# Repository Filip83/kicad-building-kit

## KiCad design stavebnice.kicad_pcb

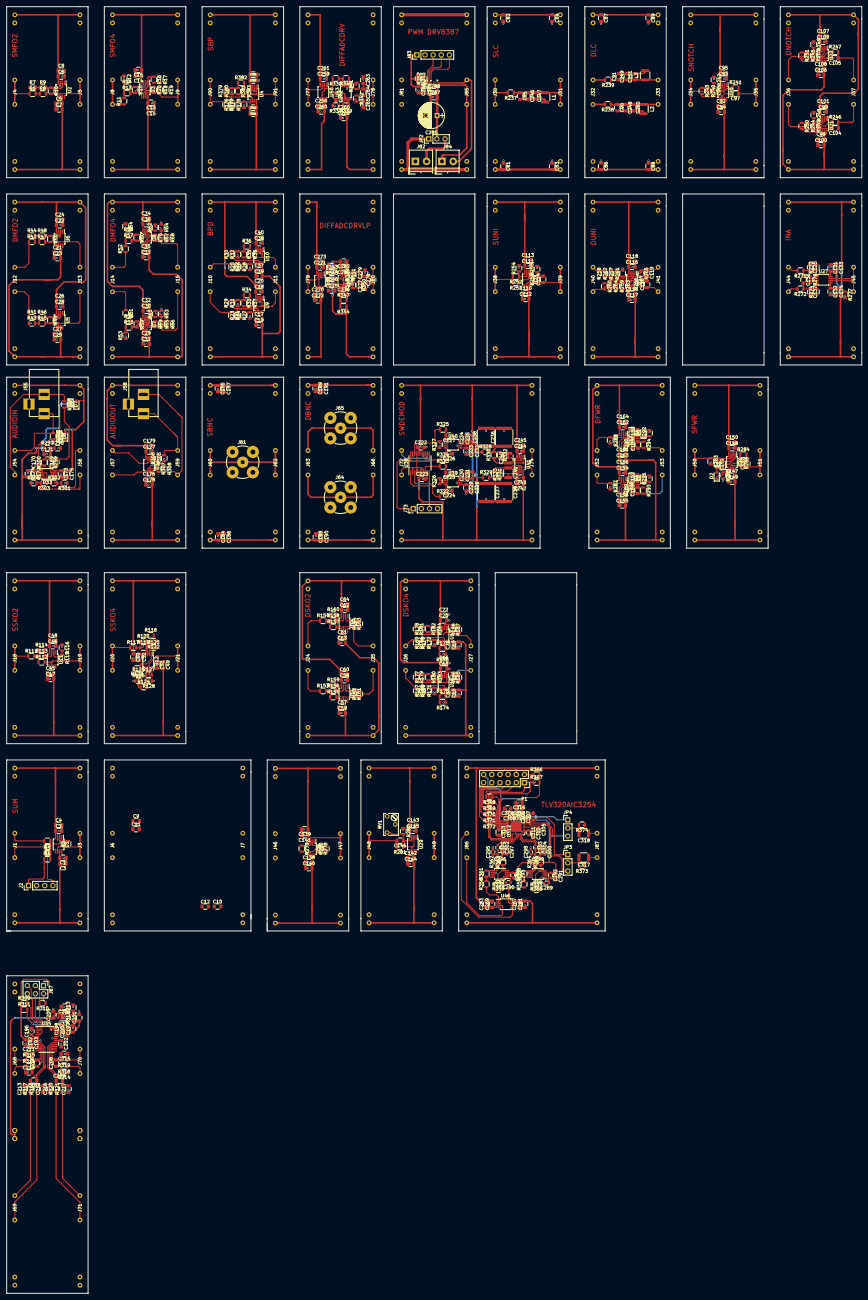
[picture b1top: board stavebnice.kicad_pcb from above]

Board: 2 copper layers, 266.7 x 401.3 mm, 676 parts (0 on the bottom side), 320 nets.

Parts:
C1, C2, C3, C4, C5, C6, C7, C8, C9, C10, C11, C12, C13, C14, C15, C16, C17, C18, C19, C20, C21, C22, C23, C24, C25, C26, C27, C28, C29, C30, C31, C32, C33, C34, C35, C36, C37, C38, C39, C40, C45, C46, C47, C48, C49, C50, C51, C52, C57, C58, C59, C60, C61, C62, C63, C64, C65, C66, C67, C68, C69, C70, C71, C72, C81, C82, C83, C84, C85, C86, C87, C88, C89, C90, C91, C92, C93, C94, C95, C96, C97, C98, C99, C100, C101, C102, C103, C104, C105, C106, C107, C108, C109, C110, C111, C112, C113, C114, C115, C116, C117, C118, C119, C120, C131, C132, C133, C134, C135, C136, C137, C138, C139, C140, C141, C142, C143, C144, C145, C146, C147, C148, C149, C150, C152, C153, C154, C155, C156, C159, C160, C161, C162, C163, C164, C169, C170, C172, C173, C174, C175, C176, C177, C178, C179, C184, C185, C186, C187, C188, C189, C190, C191, C206, C207, C208, C209, C210, C211, C212, C213, C214, C215, C216, C217, C246, C247, C248, C249, C250, C251, C258, C259, C260, C261, C263, C264, C265, C266, C267, C268, C269, C270, C271, C272, C273, C274, C275, C277, C278, C279, C280, C281, C282, C283, C319, C320, C321, C322: C; C_0805
C151, C157, C158: 47p; C_0805
C171, C205, C228, C231, C232, C235, C242, C245, C276, C287, C307, C308, C310, C316: 10u; C_0805
C192, C197, C315: 1u; C_0805
C193, C196, C198, C200, C202, C222, C223, C229, C230, C233, C234, C243, C244, C262, C284, C288: 100n; C_0805
C201, C286, C313: 4u7; C_0805
C203: 1n; C_0805
C224, C225, C226, C227: 1n5; C_0805
C236, C237, C238, C239: 470n; C_2220
C240, C241: 270n; C_1210
C285: 500u; CP_Radial_D8.0mm_P3.50mm
C289, C290, C292, C294, C295, C296, C297, C298, C299, C300, C301, C302, C303, C304, C305, C306, C309, C311, C312, C314: 100n; C_0603
C291, C293: 10u/5V; C_0805
C317, C318: C; C_1210
D1, D2, D3, D4, D5, D6: 1N4148; D_0805
D7, D8, D9, D10: D; D_0805
J1, J4, J6, J8, J10, J12, J14, J18, J20, J24, J26, J30, J32, J34, J36, J38, J40, J44, J46, J48, J50, J52, J54, J57, J60, J63, J68, J69, J70, J71, J72, J77, J79, J81, J86, J90: InConnector; my_io_connector
J2: Ext_Input; Pin_Header_Straight_1x04_Pitch2.54mm
J3, J5, J7, J9, J11, J13, J15, J19, J21, J25, J27, J31, J33, J35, J37, J39, J41, J45, J47, J49, J51, J53, J56, J59, J62, J66, J74, J78, J80, J85, J87, J91: OutConnector; my_io_connector
J55, J58: Audio-Jack-3; BARREL_JACK
J61, J64, J65: Conn_Coaxial; bnc-ci
J67: Conn_SPI; Pin_Header_Straight_2x03_Pitch2.54mm
J73: Conn_01x04; Pin_Header_Straight_1x04_Pitch2.54mm
J82, J84: Screw_Terminal_01x02; TerminalBlock_4UCON_19963_02x3.5mm_Straight
J83: Conn_01x05; Pin_Header_Straight_1x05_Pitch2.54mm
JP2, JP3, JP4: Jumper_NC_Dual; Pin_Header_Straight_1x03_Pitch2.54mm
L1, L2, L3: L; L_1210
P1: CONN_02X06; Socket_Strip_Straight_2x06
R1, R2, R3, R4, R5, R6, R7, R8, R9, R10, R11, R12, R13, R14, R15, R16, R17, R18, R19, R20, R21, R22, R23, R24, R25, R26, R27, R28, R29, R30, R31, R32, R33, R34, R35, R36, R37, R38, R41, R42, R43, R44, R45, R46, R47, R48, R49, R50, R51, R52, R53, R54, R55, R56, R57, R58, R59, R60, R61, R62, R63, R64, R65, R66, R67, R68, R69, R70, R111, R112, R113, R114, R115, R116, R117, R118, R119, R120, R121, R122, R123, R124, R125, R126, R127, R128, R153, R154, R155, R156, R157, R158, R159, R160, R161, R162, R163, R164, R165, R166, R167, R168, R169, R170, R171, R172, R173, R174, R175, R176, R177, R178, R179, R180, R181, R182, R183, R184, R185, R186, R187, R188, R237, R238, R239, R240, R241, R242, R243, R244, R245, R246, R247, R248, R249, R250, R251, R252, R253, R254, R255, R256, R257, R258, R259, R260, R261, R262, R263, R264, R265, R266, R271, R272, R273, R274, R276, R277, R278, R279, R280, R281, R282, R299, R300, R301, R302, R303, R304, R305, R306, R307, R308, R314, R315, R316, R317, R318, R319, R320, R321, R337, R338, R339, R340, R341, R342, R343, R345, R346, R350, R351, R352, R353, R373, R374, R375, R376, R377, R378, R379, R380, R381, R382, R383: R; R_0805
R283, R287, R288: 49.9; R_0805
R284, R285, R286, R289, R290, R291, R292, R293, R294: 1k; R_0805
R295, R296: 2k2; R_0805
R297, R298, R309, R310, R311, R366, R367: 10k; R_0805
R312, R313: 52k; R_0805
R322, R323, R324, R325: 5k; R_0805
R326, R327: 450; R_0805
R328, R329, R330, R331: 56k2; R_0805
R332, R333: 27k4; R_0805
R344, R347: 100k; R_0805
R348, R349: 2.49k; R_0805
R354, R355, R356, R357, R358, R359, R360, R361, R369, R370, R371, R372: 27; R_0805
R362, R363, R364, R365, R368: 10; R_0805
RV1: POT; Potentiometer_Trimmer_Bourns_3266W
U1, U2, U5, U6, U11, U14, U15, U20, U21, U22, U23, U28, U29, U50, U51: OPA333xxD; MSOP-8_3x3mm_Pitch0.65mm
U3, U7, U8, U12, U16, U17, U24, U30, U31, U32, U33, U34, U41, U44: ADA4807-2ARM; MSOP-8_3x3mm_Pitch0.65mm
U4, U9, U10, U46: ADA4075-2; MSOP-8_3x3mm_Pitch0.65mm
U27: AD8421; MSOP-8_3x3mm_Pitch0.65mm
U35: AD7124-4BRUZ; TSSOP-24_4.4x7.8mm_Pitch0.65mm
U37: ADM7170ACPZ; DFN-8-1EP_3x3mm_Pitch0.5mm
U38: ADG734BRU; TSSOP-20_4.4x6.5mm_Pitch0.65mm
U39, U40: AD8422BRMZ; MSOP-8_3x3mm_Pitch0.65mm
U43, U47, U48: LTC6363; MSOP-8_3x3mm_Pitch0.65mm
U45: DRV8837DSGR; WSON-8_2x2mm
U49: TLV320AIC3254; QFN-32-1EP_5x5mm_Pitch0.5mm

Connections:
+3.3VADC: C266.2, C268.2, C280.2, C282.2, J78.1, J80.1, R344.1, U43.3, U44.4
+3V3: C312.1, C313.1, C314.1, C315.1, C316.1, P1.4, P1.8, R366.2, R367.2, U49.6, U49.26, U49.30
+VSW: J82.2, JP2.3
/Codecs-IIS/Sheet5B5F145D//RESET: P1.12, U49.31
/Codecs-IIS/Sheet5B5F145D/Avdd: C291.1, C292.1, C293.1, C294.1, C306.1, C307.1, U47.3, U48.3, U49.24
/Codecs-IIS/Sheet5B5F145D/LRCK: P1.7, R370.2
/Codecs-IIS/Sheet5B5F145D/MCLK: P1.3, R368.2
/Codecs-IIS/Sheet5B5F145D/N1_N: C301.1, U49.13
/Codecs-IIS/Sheet5B5F145D/N1_P: C302.1, U49.14
/Codecs-IIS/Sheet5B5F145D/N2_N: C303.1, U49.15
/Codecs-IIS/Sheet5B5F145D/N2_P: C304.1, U49.16
/Codecs-IIS/Sheet5B5F145D/SCL: P1.2, R366.1, U49.9
/Codecs-IIS/Sheet5B5F145D/SCLK: P1.5, R369.2
/Codecs-IIS/Sheet5B5F145D/SDA: P1.1, R367.1, U49.10
/Codecs-IIS/Sheet5B5F145D/SIN: P1.9, R371.2
/Codecs-IIS/Sheet5B5F145D/SOUT: P1.11, R372.2
/PWM/DRV8837/8/IN1: J83.4, U45.6
/PWM/DRV8837/8/IN2: J83.5, U45.5
/PWM/DRV8837/8/~SLEEP: J83.3, R352.1, R353.2, U45.7
GND: C1.1, C2.2, C3.1, C4.2, C5.1, C6.2, C7.1, C8.2, C9.1, C10.2, C11.1, C12.2, C13.1, C14.2, C15.1, C16.2, C17.1, C18.2, C19.1, C20.2, C21.1, C22.2, C23.1, C24.2, C25.1, C26.2, C27.1, C28.2, C29.1, C30.2, C31.1, C32.2, C33.1, C34.2, C35.1, C36.2, C37.1, C38.2, C39.1, C40.2, C45.1, C46.2, C47.1, C48.2, C49.1, C50.2, C51.1, C52.2, C57.1, C58.2, C59.1, C60.2, C61.1, C62.2, C63.1, C64.2, C65.1, C66.2, C67.1, C68.2, C69.1, C70.2, C71.1, C72.2, C81.1, C82.2, C83.1, C84.2, C85.2, C86.1, C87.2, C88.1, C89.2, C90.2, C91.2, C92.1, C93.2, C94.1, C95.2, C98.1, C99.2, C100.1, C101.2, C106.1, C107.2, C108.1, C109.2, C110.1, C111.2, C112.1, C113.2, C115.1, C116.2, C117.1, C118.2, C131.1, C132.2, C133.1, C134.2, C135.1, C137.2, C138.1, C139.2, C140.1, C141.2, C142.1, C143.2, C144.1, C145.2, C147.1, C148.2, C149.1, C150.2, C153.1, C154.2, C155.1, C156.2, C161.1, C162.2, C163.1, C164.2, C171.1, C172.1, C173.2, C174.1, C175.2, C176.1, C177.2, C178.1, C179.2, C184.1, C185.2, C186.1, C187.2, C188.1, C189.2, C190.1, C191.2, C192.2, C193.2, C222.2, C223.2, C224.1, C225.1, C226.1, C227.1, C228.2, C229.2, C230.2, C231.2, C232.2, C233.2, C234.2, C235.2, C236.2, C237.2, C238.2, C239.2, C242.2, C243.2, C244.2, C245.2, C246.2, C247.2, C248.2, C249.2, C250.2, C251.2, C258.1, C259.2, C260.1, C261.2, C262.2, C263.1, C265.2, C266.1, C267.1, C268.1, C269.2, C270.1, C271.2, C272.1, C273.2, C274.2, C276.2, C277.1, C279.2, C280.1, C281.1, C282.1, C283.2, C284.2, C285.2, C286.2, C287.1, C288.1, C289.2, C290.2, C291.2, C292.2, C293.2, C294.2, C295.2, C297.1, C298.2, C300.1, C305.2, C306.2, C307.2, C308.2, C309.2, C310.2, C311.2, C312.2, C313.2, C314.2, C315.2, C316.2, C319.1, C320.2, C321.1, C322.2, J1.2, J1.5, J2.2, J2.3, J3.2, J3.5, J4.2, J4.5, J5.2, J5.5, J6.2, J6.5, J7.2, J7.5, J8.2, J8.5, J9.2, J9.5, J10.2, J10.5, J11.2, J11.5, J12.2, J12.5, J13.2, J13.5, J14.2, J14.5, J15.2, J15.5, J18.2, J18.5, J19.2, J19.5, J20.2, J20.5, J21.2, J21.5, J24.2, J24.5, J25.2, J25.5, J26.2, J26.5, J27.2, J27.5, J30.2, J30.5, J31.2, J31.5, J32.2, J32.5, J33.2, J33.5, J34.2, J34.5, J35.2, J35.5, J36.2, J36.5, J37.2, J37.5, J38.2, J38.5, J39.2, J39.5, J40.2, J40.5, J41.2, J41.5, J44.2, J44.5, J45.2, J45.5, J46.2, J46.5, J47.2, J47.5, J48.2, J48.5, J49.2, J49.5, J50.2, J50.5, J51.2, J51.5, J52.2, J52.5, J53.2, J53.5, J54.2, J54.5, J55.3, J56.2, J56.5, J57.2, J57.5, J58.3, J59.2, J59.5, J60.2, J60.5, J61.2, J62.2, J62.5, J63.2, J63.5, J64.2, J65.2, J66.2, J66.5, J67.1, J68.5, J69.1, J69.2, J70.2, J70.5, J71.2, J71.5, J72.2, J72.5, J73.2, J73.4, J74.2, J74.5, J77.2, J77.5, J78.2, J78.5, J78.6, J79.2, J79.5, J80.2, J80.5, J80.6, J81.2, J81.5, J82.1, J83.2, J85.2, J85.5, J86.2, J86.5, J87.2, J87.5, J90.2, J90.5, J91.2, J91.5, L1.2, L2.2, L3.2, P1.6, P1.10, R7.1, R12.1, R17.1, R27.1, R28.1, R31.1, R32.1, R43.1, R44.1, R53.1, R54.1, R63.1, R64.1, R114.1, R116.1, R120.1, R122.1, R126.1, R128.1, R159.1, R160.1, R162.1, R164.1, R171.1, R172.1, R174.1, R176.1, R183.1, R184.1, R186.1, R188.1, R242.1, R248.1, R249.1, R254.2, R255.2, R261.2, R262.2, R263.2, R264.2, R273.2, R274.1, R277.2, R278.2, R282.1, R283.2, R285.2, R287.2, R288.2, R291.2, R292.2, R298.2, R301.1, R304.1, R305.1, R308.1, R337.2, R347.2, R353.1, R355.1, R357.1, R373.1, R374.1, R378.1, R380.1, RV1.1, RV1.2, U1.3, U2.3, U3.3, U3.5, U4.2, U5.3, U6.3, U7.3, U7.5, U8.3, U8.5, U9.2, U10.2, U38.4, U38.6, U38.9, U38.14, U38.19, U39.6, U40.6, U41.3, U41.5, U43.6, U44.8, U45.4, U45.9, U47.6, U48.6, U49.7, U49.12, U49.17, U49.28, U49.33
GNDA: C196.2, C197.2, C198.2, C200.2, C201.2, C202.2, C203.2, C205.2, C210.1, C211.1, C212.1, C213.1, C214.1, C215.1, C216.1, C217.1, R313.2, U35.7, U35.19, U37.6, U37.9
unnamed: C96.1, R242.2, U20.3
unnamed: C96.2, J34.3, J34.4, R240.2, R241.1
unnamed: C97.1, J35.3, J35.4, R241.2
unnamed: C97.2, R243.2, U20.6
unnamed: C102.1, R248.2, U21.3
unnamed: C102.2, J36.3, R244.2, R246.1
unnamed: C103.1, R249.2, U22.3
unnamed: C103.2, J36.4, R245.2, R247.1
unnamed: C104.1, J37.3, R246.2
unnamed: C104.2, R250.2, U21.6
unnamed: C105.1, J37.4, R247.2
unnamed: C105.2, R251.2, U22.6
unnamed: C114.1, J39.3, J39.4, R256.1, U23.6
unnamed: C114.2, R253.1, R255.1, R256.2, U23.2
unnamed: C119.1, J41.4, R265.1, U24.1
unnamed: C119.2, R258.1, R262.1, R265.2, U24.2
unnamed: C120.1, J41.3, R266.1, U24.7
unnamed: C120.2, R260.1, R264.1, R266.2, U24.6
unnamed: C135.2, C136.1, R271.1, R273.1, U27.1
unnamed: C136.2, C137.1, R272.1, R274.2, U27.4
unnamed: C146.1, R282.2, RV1.3, U29.3
unnamed: C146.2, J48.3, J48.4, R281.2
unnamed: C151.1, D1.2, R284.1, U30.2
unnamed: C151.2, D1.1, D2.2, U30.1
unnamed: C152.1, J51.3, J51.4, R286.2, U30.7
unnamed: C152.2, R284.2, R286.1, U30.6
unnamed: C157.1, D3.2, R289.1, U31.2
unnamed: C157.2, D3.1, D5.2, U31.1
unnamed: C158.1, D4.2, R290.1, U32.2
unnamed: C158.2, D4.1, D6.2, U32.1
unnamed: C159.1, J53.3, R293.2, U31.7
unnamed: C159.2, R289.2, R293.1, U31.6
unnamed: C160.1, J53.4, R294.2, U32.7
unnamed: C160.2, R290.2, R294.1, U32.6
unnamed: C169.1, R299.2, U33.3
unnamed: C169.2, D7.2, D9.1, R295.2
unnamed: C170.1, R300.1, U33.5
unnamed: C170.2, D8.2, D10.1, R296.2
unnamed: C171.2, R297.2, R298.1, R299.1, R300.2
unnamed: C196.1, U35.5
unnamed: C197.1, C198.1, C201.1, R312.1, U35.22, U37.1, U37.2
unnamed: C200.1, U35.20
unnamed: C202.1, U35.18
unnamed: C203.1, U37.4
unnamed: C206.1, C210.2, R314.2, U35.10
unnamed: C206.2, C211.2, R315.2, U35.11
unnamed: C207.1, C212.2, R316.2, U35.8
unnamed: C207.2, C213.2, R317.2, U35.9
unnamed: C208.1, C214.2, R318.2, U35.15
unnamed: C208.2, C215.2, R319.2, U35.14
unnamed: C209.1, C216.2, R320.2, U35.17
unnamed: C209.2, C217.2, R321.2, U35.16
unnamed: C224.2, R322.2, U39.4
unnamed: C225.2, R323.2, U39.1
unnamed: C226.2, R324.2, U40.4
unnamed: C227.2, R325.2, U40.1
unnamed: C236.1, C238.1, R328.2, R330.2, R332.1
unnamed: C237.1, C239.1, R329.2, R331.2, R333.1
unnamed: C240.1, J74.4, R330.1, U41.1
unnamed: C240.2, R332.2, U41.2
unnamed: C241.1, J74.3, R331.1, U41.7
unnamed: C241.2, R333.2, U41.6
unnamed: C85.1, C246.1, C247.1, J31.3, J31.4, L1.1, R237.1
unnamed: C90.1, C248.1, C250.1, J33.3, L2.1, R238.1
unnamed: C91.1, C249.1, C251.1, J33.4, L3.1, R239.1
unnamed: C262.1, U43.2
unnamed: C263.2, C264.1, J78.4, R341.1
unnamed: C264.2, C265.1, J78.3, R342.1
unnamed: C274.1, R343.2, R345.1, R346.1
unnamed: C275.1, R345.2, R348.1, R350.2, U44.7
unnamed: C275.2, R346.2, U44.6
unnamed: C276.1, R344.2, R347.1, U44.3, U44.5
unnamed: C277.2, C278.1, J80.3, R350.1
unnamed: C278.2, C279.1, J80.4, R351.1
unnamed: C285.1, C287.2, C288.2, JP2.2, U45.1
unnamed: C289.1, U48.2
unnamed: C290.1, U47.2
unnamed: C295.1, C296.2, C301.2, R362.2
unnamed: C296.1, C297.2, C302.2, R363.2
unnamed: C298.1, C299.2, C303.2, R364.2
unnamed: C299.1, C300.2, C304.2, R365.2
unnamed: C305.1, U49.20, U49.21
unnamed: C308.1, C309.1, U49.29
unnamed: C310.1, C311.1, U49.18
unnamed: C317.1, J87.3
unnamed: C317.2, JP3.2, R373.2
unnamed: C318.1, J87.4
unnamed: C318.2, JP4.2, R374.2
unnamed: D2.1, R285.1, U30.5
unnamed: D5.1, R291.1, U31.5
unnamed: D6.1, R292.1, U32.5
unnamed: J1.3, R1.2
unnamed: J1.4, R2.2
unnamed: J2.1, R4.1
unnamed: J2.4, R3.1
unnamed: J3.3, J3.4, R5.1, U1.6
unnamed: J4.3, J4.4, R6.1
unnamed: J5.3, J5.4, R8.2, R10.2, U2.6
unnamed: J7.3, J7.4
unnamed: J8.3, J8.4, R11.1
unnamed: J9.3, J9.4, R18.2, R20.2, U3.7
unnamed: J10.3, R21.1
unnamed: J10.4, R22.1
unnamed: J11.3, R33.2, R37.2, U9.1
unnamed: J11.4, R35.2, R38.2, U10.1
unnamed: J12.3, R41.1
unnamed: J12.4, R42.1
unnamed: J13.3, R45.2, R49.2, U5.6
unnamed: J13.4, R47.2, R50.2, U6.6
unnamed: J14.3, R51.1
unnamed: J14.4, R52.1
unnamed: J15.3, R65.2, R69.2, U7.7
unnamed: J15.4, R67.2, R70.2, U8.7
unnamed: J18.3, J18.4, R111.1
unnamed: J19.3, J19.4, R112.2, R115.2, U11.6
unnamed: J20.3, J20.4, R117.1
unnamed: J21.3, J21.4, R124.2, R127.2, U12.7
unnamed: J24.3, R153.1
unnamed: J24.4, R154.1
unnamed: J25.3, R155.2, R161.2, U14.6
unnamed: J25.4, R157.2, R163.2, U15.6
unnamed: J26.3, R165.1
unnamed: J26.4, R166.1
unnamed: J27.3, R179.2, R185.2, U16.1
unnamed: J27.4, R181.2, R187.2, U17.1
unnamed: J30.3, J30.4, R237.2
unnamed: J32.3, R238.2
unnamed: J32.4, R239.2
unnamed: J38.3, J38.4, R252.2, R253.2
unnamed: J40.3, R259.2, R260.2
unnamed: J40.4, R257.2, R258.2
unnamed: J44.3, R272.2
unnamed: J44.4, R271.2
unnamed: J45.3, R277.1, U27.6
unnamed: J45.4, U27.7
unnamed: J47.3, J47.4, R279.1, U28.3
unnamed: J49.3, J49.4
unnamed: J50.3, J50.4, R283.1, U30.3
unnamed: J52.3, R287.1, U31.3
unnamed: J52.4, R288.1, U32.3
unnamed: J54.3, J55.2, R295.1
unnamed: J54.4, J55.1, R296.1
unnamed: J56.3, R303.2, R304.2, U33.7
unnamed: J56.4, R301.2, R302.2, U33.1
unnamed: J57.3, U34.5
unnamed: J57.4, U34.3
unnamed: J58.1, J59.4, R305.2, R306.2, U34.1
unnamed: J58.2, J59.3, R307.2, R308.2, U34.7
unnamed: J60.3, J60.4, J61.1, J62.3, J62.4
unnamed: J63.3, J64.1, J66.3
unnamed: J63.4, J65.1, J66.4
unnamed: J67.3, R310.2, U35.4
unnamed: J67.4, U35.2
unnamed: J67.5, U35.1
unnamed: J67.6, R309.2, U35.24
unnamed: J68.3, R314.1
unnamed: J68.4, R315.1
unnamed: J69.3, R316.1
unnamed: J69.4, R317.1
unnamed: J70.3, R318.1
unnamed: J70.4, R319.1
unnamed: J71.3, R320.1
unnamed: J71.4, R321.1
unnamed: J72.3, J72.4, U38.2, U38.7, U38.12, U38.17
unnamed: J73.1, U38.11, U38.20
unnamed: J73.3, U38.1, U38.10
unnamed: J77.3, J77.4, U50.3
unnamed: J79.3, J79.4, U51.3
unnamed: J84.1, J85.3, U45.2
unnamed: J84.2, J85.4, U45.3
unnamed: J86.3, U46.3
unnamed: J86.4, U46.5
unnamed: J90.3, J90.4, R375.1
unnamed: J91.3, J91.4, R381.2, R383.2, U4.1
unnamed: JP3.1, U49.25
unnamed: JP3.3, U49.22
unnamed: JP4.1, U49.27
unnamed: JP4.3, U49.23
unnamed: R1.1, R2.1, R3.2, R4.2, R5.2, U1.2
unnamed: R6.2, R7.2, R8.1, R9.1
unnamed: R9.2, R10.1, U2.2
unnamed: R11.2, R12.2, R13.1, R14.1
unnamed: R13.2, R15.2, R16.1, U3.1
unnamed: R14.2, R15.1, U3.2
unnamed: R16.2, R17.2, R18.1, R19.1
unnamed: R19.2, R20.1, U3.6
unnamed: R21.2, R23.1, R24.1
unnamed: R22.2, R25.1, R26.1
unnamed: R23.2, R29.1, U9.6, U9.7
unnamed: R24.2, R27.2, U9.5
unnamed: R25.2, R30.1, U10.6, U10.7
unnamed: R26.2, R28.2, U10.5
unnamed: R29.2, R31.2, R33.1, R34.1
unnamed: R30.2, R32.2, R35.1, R36.1
unnamed: R34.2, R37.1, U9.3
unnamed: R36.2, R38.1, U10.3
unnamed: R41.2, R43.2, R45.1, R46.1
unnamed: R42.2, R44.2, R47.1, R48.1
unnamed: R46.2, R49.1, U5.2
unnamed: R48.2, R50.1, U6.2
unnamed: R51.2, R53.2, R55.1, R56.1
unnamed: R52.2, R54.2, R57.1, R58.1
unnamed: R55.2, R59.2, R61.1, U7.1
unnamed: R56.2, R59.1, U7.2
unnamed: R57.2, R60.2, R62.1, U8.1
unnamed: R58.2, R60.1, U8.2
unnamed: R61.2, R63.2, R65.1, R66.1
unnamed: R62.2, R64.2, R67.1, R68.1
unnamed: R66.2, R69.1, U7.6
unnamed: R68.2, R70.1, U8.6
unnamed: R111.2, R112.1, R113.1
unnamed: R113.2, R114.2, U11.3
unnamed: R115.1, R116.2, U11.2
unnamed: R117.2, R118.1, R119.1
unnamed: R118.2, R121.2, R123.1, U12.1
unnamed: R119.2, R120.2, U12.3
unnamed: R121.1, R122.2, U12.2
unnamed: R123.2, R124.1, R125.1
unnamed: R125.2, R126.2, U12.5
unnamed: R127.1, R128.2, U12.6
unnamed: R153.2, R155.1, R156.1
unnamed: R154.2, R157.1, R158.1
unnamed: R156.2, R159.2, U14.3
unnamed: R158.2, R160.2, U15.3
unnamed: R161.1, R162.2, U14.2
unnamed: R163.1, R164.2, U15.2
unnamed: R165.2, R167.1, R168.1
unnamed: R166.2, R169.1, R170.1
unnamed: R167.2, R173.2, R177.1, U16.7
unnamed: R168.2, R171.2, U16.5
unnamed: R169.2, R175.2, R178.1, U17.7
unnamed: R170.2, R172.2, U17.5
unnamed: R173.1, R174.2, U16.6
unnamed: R175.1, R176.2, U17.6
unnamed: R177.2, R179.1, R180.1
unnamed: R178.2, R181.1, R182.1
unnamed: R180.2, R183.2, U16.3
unnamed: R182.2, R184.2, U17.3
unnamed: R185.1, R186.2, U16.2
unnamed: R187.1, R188.2, U17.2
unnamed: R240.1, R243.1, U20.2
unnamed: R244.1, R250.1, U21.2
unnamed: R245.1, R251.1, U22.2
unnamed: R252.1, R254.1, U23.3
unnamed: R257.1, R261.1, U24.3
unnamed: R259.1, R263.1, U24.5
unnamed: R276.1, U27.2
unnamed: R276.2, U27.3
unnamed: R278.1, R280.2, U28.2
unnamed: R279.2, R280.1, U28.6
unnamed: R281.1, U29.2, U29.6
unnamed: R302.1, U33.2
unnamed: R303.1, U33.6
unnamed: R306.1, U34.2
unnamed: R307.1, U34.6
unnamed: R311.2, U35.23
unnamed: R312.2, R313.1, U37.3
unnamed: R322.1, U38.3
unnamed: R323.1, U38.8
unnamed: R324.1, U38.13
unnamed: R325.1, U38.18
unnamed: R326.1, U39.3
unnamed: R326.2, U39.2
unnamed: R327.1, U40.3
unnamed: R327.2, U40.2
unnamed: R328.1, U40.7
unnamed: R329.1, U39.7
unnamed: R337.1, R339.2, U43.1
unnamed: R338.1, R340.2, U43.8
unnamed: R338.2, U50.2, U50.6
unnamed: R339.1, R342.2, U43.4
unnamed: R340.1, R341.2, U43.5
unnamed: R343.1, U51.2, U51.6
unnamed: R348.2, R349.1, U44.2
unnamed: R349.2, R351.2, U44.1
unnamed: R354.1, U46.6, U46.7
unnamed: R354.2, R358.1, U48.8
unnamed: R355.2, R359.1, U47.1
unnamed: R356.1, U46.1, U46.2
unnamed: R356.2, R361.1, U47.8
unnamed: R357.2, R360.1, U48.1
unnamed: R358.2, R364.1, U48.5
unnamed: R359.2, R363.1, U47.4
unnamed: R360.2, R365.1, U48.4
unnamed: R361.2, R362.1, U47.5
unnamed: R368.1, U49.1
unnamed: R369.1, U49.2
unnamed: R370.1, U49.3
unnamed: R371.1, U49.4
unnamed: R372.1, U49.5
unnamed: R375.2, R376.1, R377.1
unnamed: R376.2, R379.1, U4.6, U4.7
unnamed: R377.2, R378.2, U4.5
unnamed: R379.2, R380.2, R381.1, R382.1
unnamed: R382.2, R383.1, U4.3
V+: C284.1, C286.1, J83.1, R352.2, U45.8
VBUS: C192.1, C193.1, J67.2, R309.1, R310.1, R311.1, U35.6
VCC: C1.2, C3.2, C5.2, C7.2, C9.2, C11.2, C13.2, C15.2, C17.2, C19.2, C21.2, C23.2, C25.2, C27.2, C29.2, C31.2, C33.2, C35.2, C37.2, C39.2, C45.2, C47.2, C49.2, C51.2, C57.2, C59.2, C61.2, C63.2, C65.2, C67.2, C69.2, C71.2, C81.2, C83.2, C86.2, C88.2, C92.2, C94.2, C98.2, C100.2, C106.2, C108.2, C110.2, C112.2, C115.2, C117.2, C131.2, C133.2, C138.2, C140.2, C142.2, C144.2, C147.2, C149.2, C153.2, C155.2, C161.2, C163.2, C172.2, C174.2, C176.2, C178.2, C184.2, C186.2, C188.2, C190.2, C205.1, C223.1, C230.1, C231.1, C234.1, C235.1, C242.1, C243.1, C258.2, C260.2, C267.2, C270.2, C272.2, C281.2, C319.2, C321.2, D7.1, D8.1, J1.1, J3.1, J4.1, J5.1, J6.1, J7.1, J8.1, J9.1, J10.1, J11.1, J12.1, J13.1, J14.1, J15.1, J18.1, J19.1, J20.1, J21.1, J24.1, J25.1, J26.1, J27.1, J30.1, J31.1, J32.1, J33.1, J34.1, J35.1, J36.1, J37.1, J38.1, J39.1, J40.1, J41.1, J44.1, J45.1, J46.1, J47.1, J48.1, J49.1, J50.1, J51.1, J52.1, J53.1, J54.1, J56.1, J57.1, J59.1, J60.1, J62.1, J63.1, J66.1, J68.1, J68.2, J69.5, J69.6, J72.1, J74.1, J77.1, J79.1, J81.1, J85.1, J86.1, J87.1, J90.1, J91.1, JP2.1, R297.1, U1.7, U2.7, U3.8, U4.8, U5.7, U6.7, U7.8, U8.8, U9.8, U10.8, U11.7, U12.8, U14.7, U15.7, U16.8, U17.8, U20.7, U21.7, U22.7, U23.7, U24.8, U27.8, U28.7, U29.7, U30.8, U31.8, U32.8, U33.8, U34.8, U37.5, U37.7, U37.8, U38.5, U39.8, U40.8, U41.8, U46.8, U50.7, U51.7
VSS: C2.1, C4.1, C6.1, C8.1, C10.1, C12.1, C14.1, C16.1, C18.1, C20.1, C22.1, C24.1, C26.1, C28.1, C30.1, C32.1, C34.1, C36.1, C38.1, C40.1, C46.1, C48.1, C50.1, C52.1, C58.1, C60.1, C62.1, C64.1, C66.1, C68.1, C70.1, C72.1, C82.1, C84.1, C87.1, C89.1, C93.1, C95.1, C99.1, C101.1, C107.1, C109.1, C111.1, C113.1, C116.1, C118.1, C132.1, C134.1, C139.1, C141.1, C143.1, C145.1, C148.1, C150.1, C154.1, C156.1, C162.1, C164.1, C173.1, C175.1, C177.1, C179.1, C185.1, C187.1, C189.1, C191.1, C222.1, C228.1, C229.1, C232.1, C233.1, C244.1, C245.1, C259.1, C261.1, C269.1, C271.1, C273.1, C283.1, C320.1, C322.1, D9.2, D10.2, J1.6, J3.6, J4.6, J5.6, J6.6, J7.6, J8.6, J9.6, J10.6, J11.6, J12.6, J13.6, J14.6, J15.6, J18.6, J19.6, J20.6, J21.6, J24.6, J25.6, J26.6, J27.6, J30.6, J31.6, J32.6, J33.6, J34.6, J35.6, J36.6, J37.6, J38.6, J39.6, J40.6, J41.6, J44.6, J45.6, J46.6, J47.6, J48.6, J49.6, J50.6, J51.6, J52.6, J53.6, J54.6, J56.6, J57.6, J59.6, J60.6, J62.6, J63.6, J66.6, J68.6, J72.6, J74.6, J77.6, J79.6, J81.6, J85.6, J86.6, J87.6, J90.6, J91.6, U1.4, U2.4, U3.4, U4.4, U5.4, U6.4, U7.4, U8.4, U9.4, U10.4, U11.4, U12.4, U14.4, U15.4, U16.4, U17.4, U20.4, U21.4, U22.4, U23.4, U24.4, U27.5, U28.4, U29.4, U30.4, U31.4, U32.4, U33.4, U34.4, U38.16, U39.5, U40.5, U41.4, U46.4, U50.4, U51.4
